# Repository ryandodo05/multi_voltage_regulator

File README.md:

# 🔌 Multi-Output Voltage Regulator (3.3V / 5V / 12V)

## 📌 Overview

This project is a **compact analog voltage regulator module** designed to provide three independent regulated outputs: **3.3V, 5V, and 12V**.  

It allows flexible input/output routing and integrates an **IRL MOSFET power stage** to handle higher currents reliably. The design is modular and can be easily integrated into other analog systems or DIY electronics projects.

---

## ⚙️ Features

- Three regulated voltage outputs: **3.3V, 5V, 12V**
- Independent input/output connections
- High-current handling with IRL MOSFET
- Compact PCB layout suitable for integration
- Fully analog design (no microcontrollers)
- Modular and flexible for different projects

---

## 📷 Screenshots

### Schematic (work in progress)

### PCB Layout

### Power Stage with IRL MOSFET

---

## 🛠️ Technical Specifications

- Input voltage: depends on desired regulation range (ensure Vin > Vout + dropout)
- Output voltages: 3.3V, 5V, 12V
- Output current: determined by MOSFET and heat dissipation
- Regulation type: linear / LDO style
- Analog protection and filtering included
- PCB designed for modular integration

---

## 🎯 Objectives

- Provide multiple regulated voltages from a single module
- Ensure stable outputs for analog and digital systems
- Offer a flexible, high-current design for DIY projects
- Document the design with schematics and PCB screenshots for reference

---

## 🚀 Future Improvements

- Test and optimize thermal performance
- Validate load stability and voltage ripple
- Add overcurrent and overvoltage protection
- Modular expansion for additional voltage rails
- Create a ready-to-use kit for hobbyists and engineers

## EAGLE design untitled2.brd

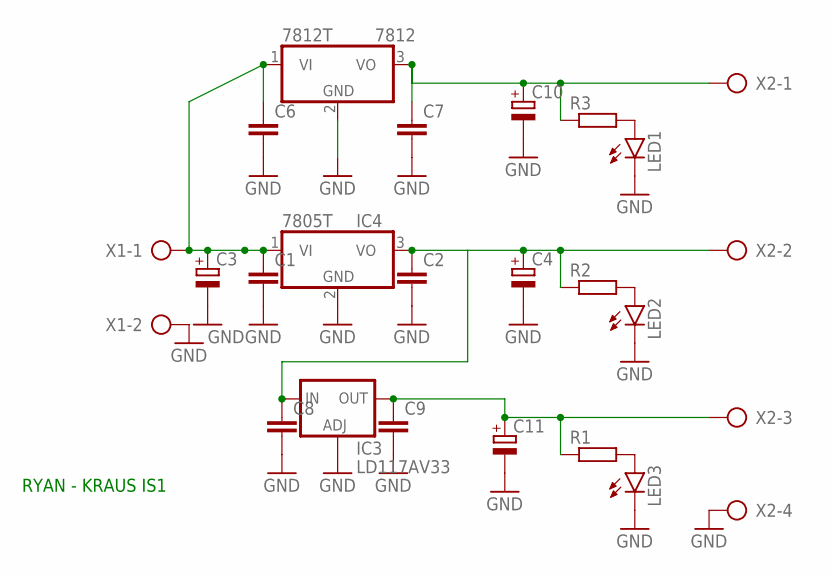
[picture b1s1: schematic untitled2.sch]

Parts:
7812: 7812T; TO220H
C1, C2, C6, C7, C8, C9: C-EU050-025X075; C050-025X075
C3: CPOL-EUE5-13; E5-13
C4, C10, C11: CPOL-EUE5-6; E5-6
IC3: LD117AV33; TO220L1
IC4: 7805T; TO220H
LED1, LED2, LED3: LED5MM
R1, R2, R3: R-EU_0204/7; 0204/7
X1: AK300/2
X2: AK300/4

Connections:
GND: 7812.2 (GND), C1.2, C2.2, C3.-, C4.-, C6.2, C7.2, C8.2, C9.2, C10.-, C11.-, IC3.1 (ADJ), IC4.2 (GND), LED1.K (C), LED2.K (C), LED3.K (C), X1.2, X2.4
unnamed: 7812.1 (VI), C1.1, C3.+, C6.1, IC4.1 (VI), X1.1
unnamed: C2.1, C4.+, C8.1, IC3.3 (IN), IC4.3 (VO), R2.1, X2.2
unnamed: C9.1, C11.+, IC3.2 (OUT), R1.1, X2.3
unnamed: 7812.3 (VO), C7.1, C10.+, R3.1, X2.1
unnamed: LED3.A, R1.2
unnamed: LED2.A, R2.2
unnamed: LED1.A, R3.2

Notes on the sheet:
RYAN - KRAUS IS1

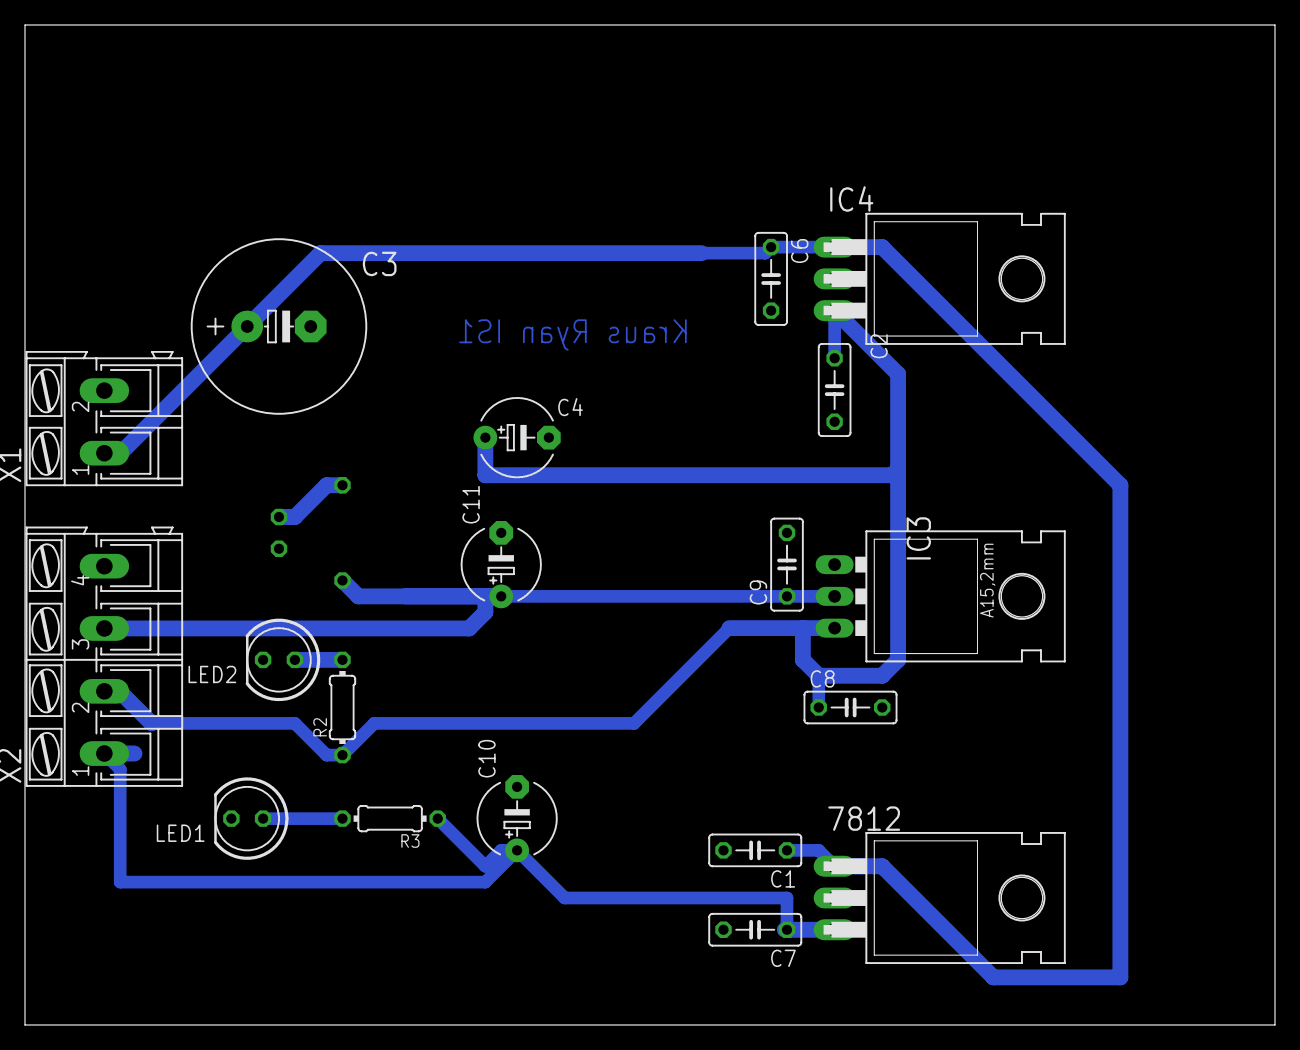
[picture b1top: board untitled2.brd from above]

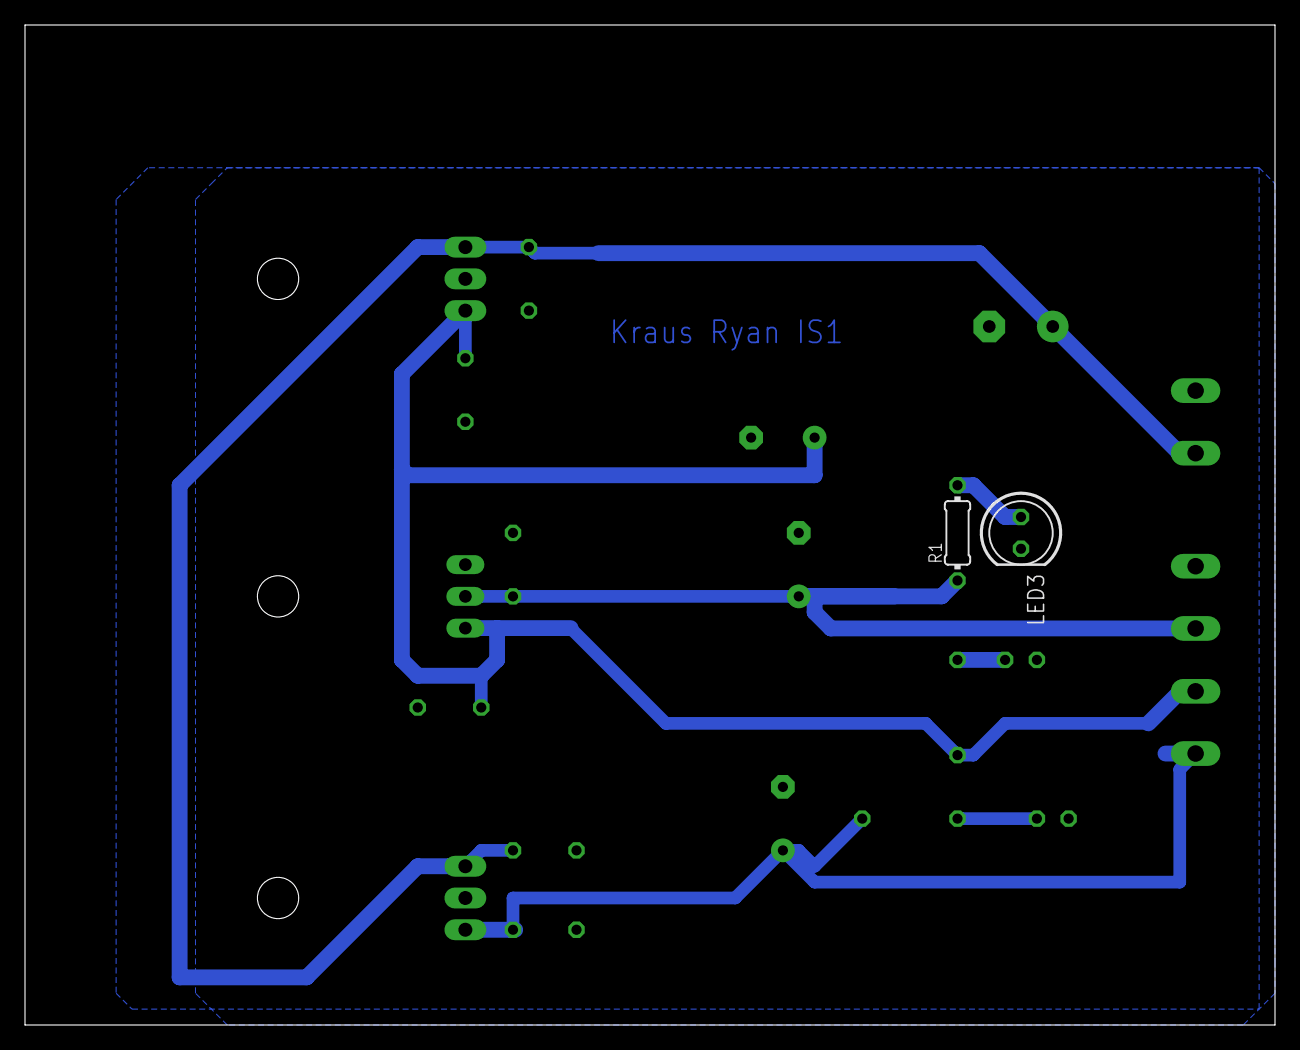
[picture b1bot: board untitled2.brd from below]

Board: 2 copper layers, 100.0 x 80.0 mm, 21 parts (2 on the bottom side), 8 nets.

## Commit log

2026-02-17 Make readme
2026-02-17 Add initial schematic and PCB screenshots for multi-output voltage regulator
2026-02-17 Rename brd.png to pcb.png
